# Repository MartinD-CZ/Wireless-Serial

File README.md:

# Wireless-Serial

*see the Instructable [here]()!*

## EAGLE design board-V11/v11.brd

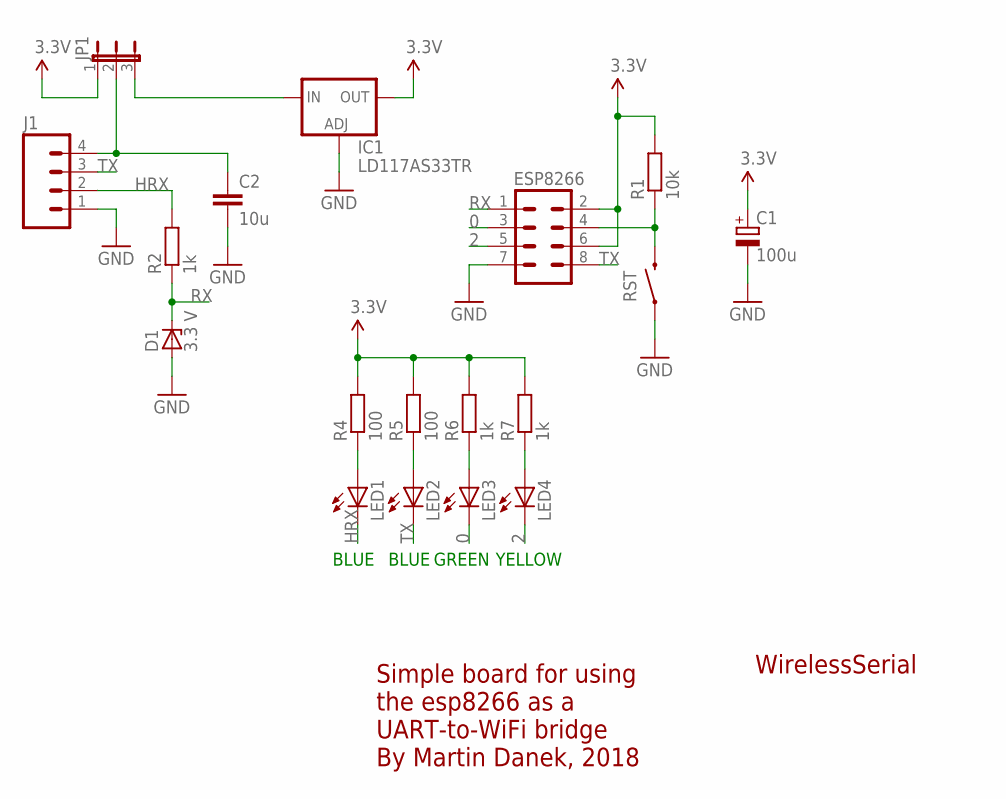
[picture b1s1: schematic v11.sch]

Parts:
C1: 100u; E2,5-6E
C2: 10u; C1206
D1: 3.3 V; DO35Z10
ESP8266: M04X2; 2X4
IC1: LD117AS33TR; SOT223
J1: M04LONGPADS; 1X04_LONGPADS
JP1: JP2E; JP2
LED1, LED2, LED3, LED4: LEDSML1206; SML1206
R1: 10k; R1206
R2, R6, R7: 1k; R1206
R4, R5: 100; R1206
RST: SWITCH-MOMENTARY-2PTH; TACTILE-PTH

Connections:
0: ESP8266.3, LED3.C
2: ESP8266.5, LED4.C
3.3V: C1.+, ESP8266.2, ESP8266.6, IC1.4 (OUT), JP1.1, R1.2, R4.2, R5.2, R6.2, R7.2
GND: C1.-, C2.2, D1.A, ESP8266.7, IC1.1 (ADJ), J1.1, RST.1
HRX: J1.2, LED1.C, R2.2
unnamed: C2.1, J1.4, JP1.2
unnamed: ESP8266.4, R1.1, RST.3 (2)
unnamed: IC1.3 (IN), JP1.3
unnamed: LED1.A, R4.1
unnamed: LED2.A, R5.1
unnamed: LED3.A, R6.1
unnamed: LED4.A, R7.1
RX: D1.C, ESP8266.1, R2.1
TX: ESP8266.8, J1.3, LED2.C

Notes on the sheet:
BLUE
GREEN
YELLOW
WirelessSerial
Simple board for using the esp8266 as a UART-to-WiFi bridge By Martin Danek, 2018

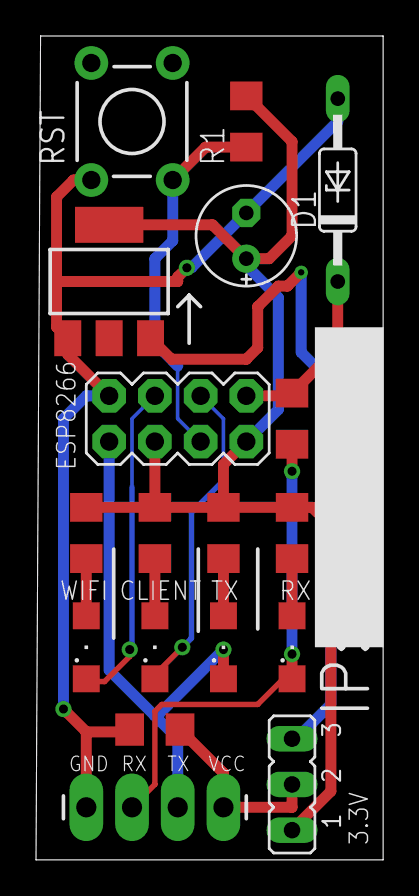
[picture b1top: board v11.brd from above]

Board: 2 copper layers, 19.3 x 45.8 mm, 18 parts (0 on the bottom side), 14 nets.

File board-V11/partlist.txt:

Partlist

Exported from v11.sch at 15.01.2018 16:53

EAGLE Version 8.4.1 Copyright (c) 1988-2017 Autodesk, Inc.

Assembly variant: 

Part     Value                 Device                Package       Library                    Sheet

C1       100u                  CPOL-EUE2,5-6E        E2,5-6E       resistor                   1
C2       10u                   C-EUC1206             C1206         resistor                   1
D1       3.3 V                 ZENER-DIODEDO35Z10    DO35Z10       diode                      1
ESP8266                        M04X2                 2X4           SparkFun-Connectors        1
IC1      LD117AS33TR           LD117AS33TR           SOT223        v-reg                      1
J1                             M04LONGPADS           1X04_LONGPADS SparkFun-Connectors        1
JP1                            JP2E                  JP2           jumper                     1
LED1                           LEDSML1206            SML1206       led                        1
LED2                           LEDSML1206            SML1206       led                        1
LED3                           LEDSML1206            SML1206       led                        1
LED4                           LEDSML1206            SML1206       led                        1
R1       10k                   R-EU_R1206            R1206         resistor                   1
R2       1k                    R-EU_R1206            R1206         resistor                   1
R4       100                   R-EU_R1206            R1206         resistor                   1
R5       100                   R-EU_R1206            R1206         resistor                   1
R6       1k                    R-EU_R1206            R1206         resistor                   1
R7       1k                    R-EU_R1206            R1206         resistor                   1
RST      SWITCH-MOMENTARY-2PTH SWITCH-MOMENTARY-2PTH TACTILE-PTH   SparkFun-Electromechanical 1

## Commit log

2018-01-17 initial release
    (initial release)

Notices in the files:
parts and their libraries:
SparkFun-Connectors: Licensing: Creative Commons ShareAlike 4.0 International - https://creativecommons.org/licenses/by-sa/4.0
